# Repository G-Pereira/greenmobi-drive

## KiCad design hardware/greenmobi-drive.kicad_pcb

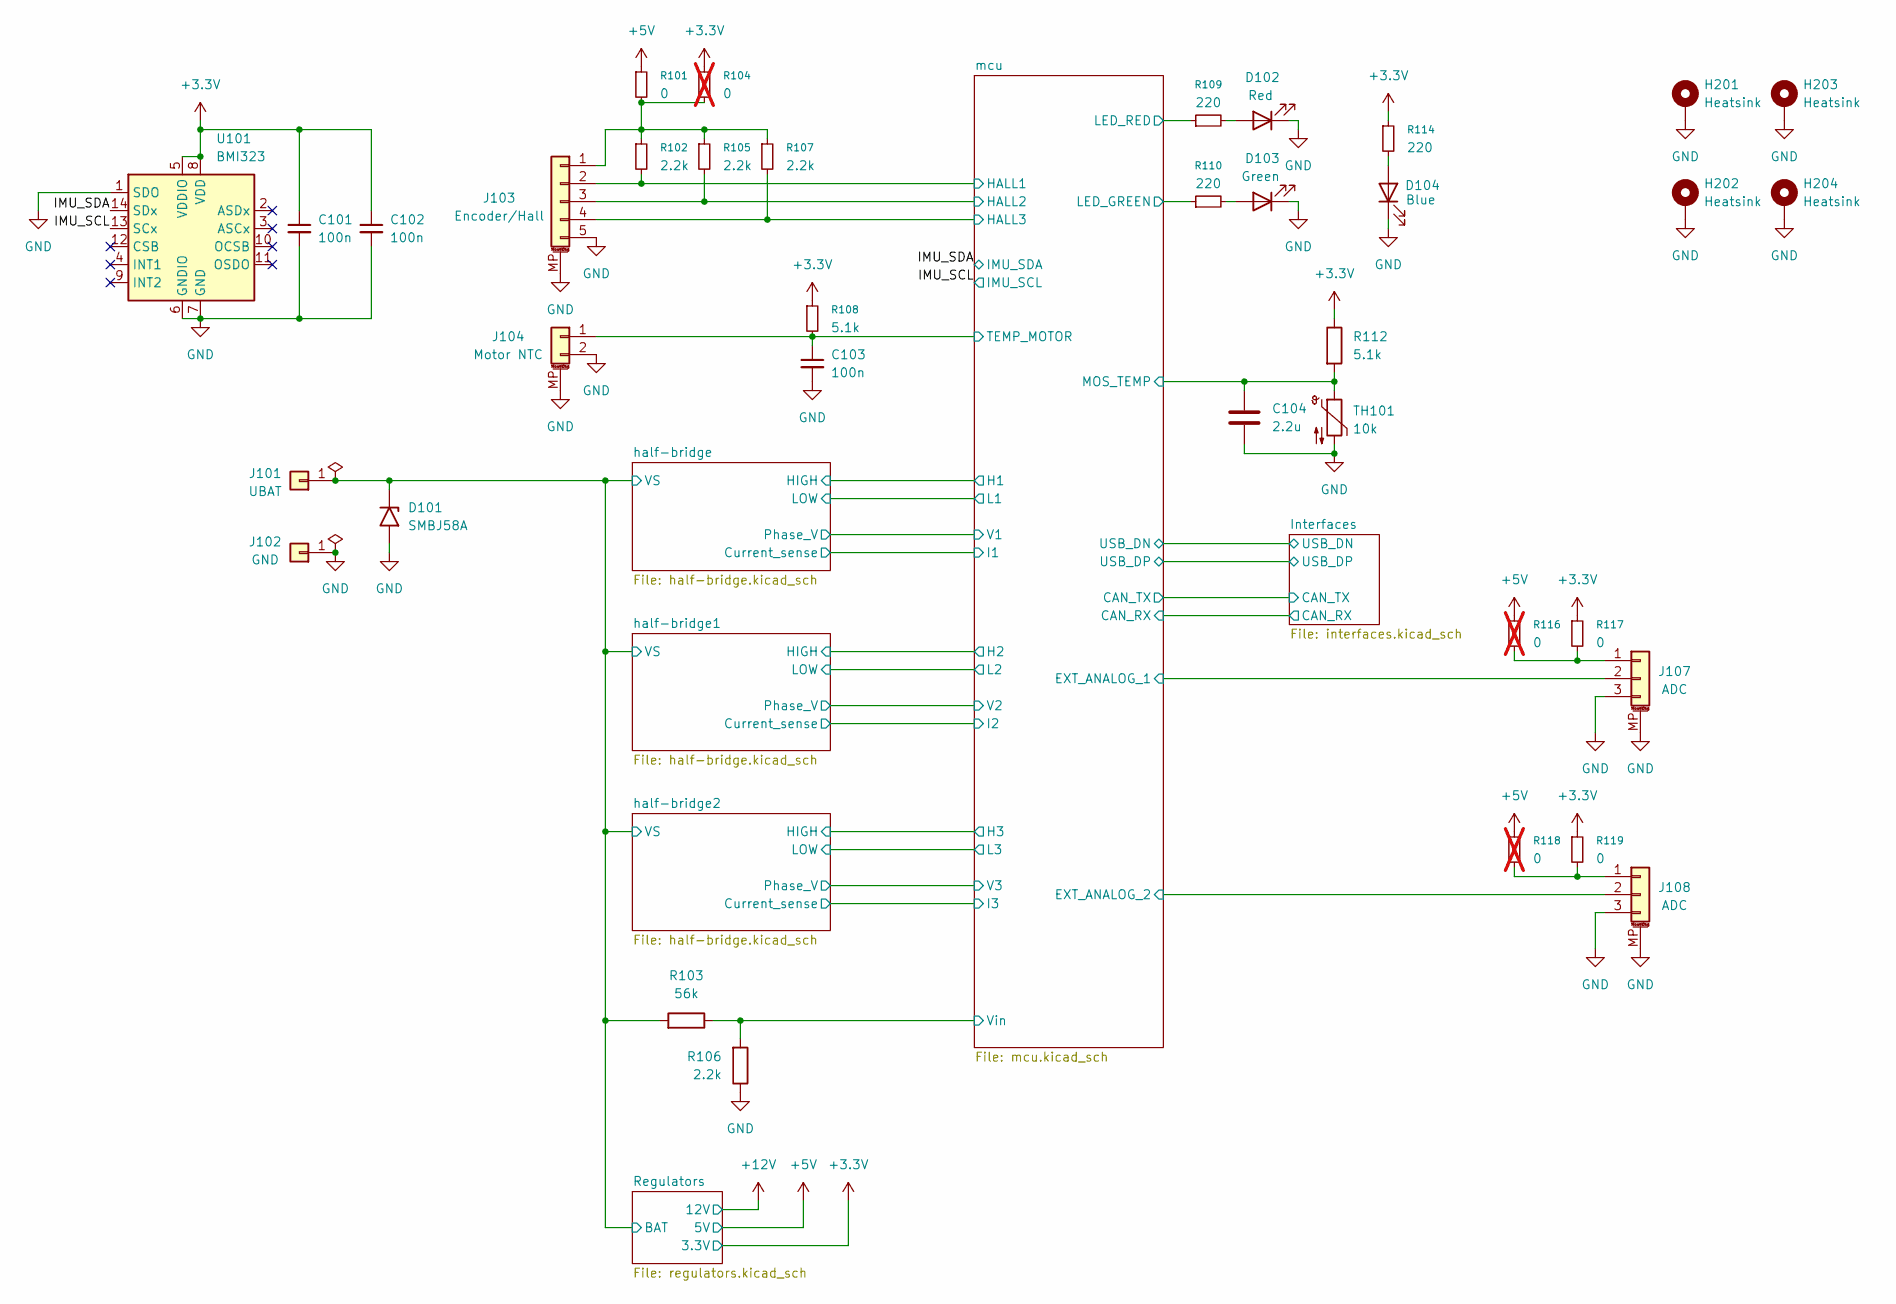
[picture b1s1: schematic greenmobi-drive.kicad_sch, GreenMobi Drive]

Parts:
C101, C102, C103: 100n; C_0402_1005Metric; LCSC C77020
C104: 2.2u; C_0402_1005Metric; LCSC C170151
D101: SMBJ58A; D_SMB; LCSC C151910
D102: Red; LED_0805_2012Metric; LCSC C688884
D103: Green; LED_0805_2012Metric; LCSC C688883
D104: Blue; LED_0805_2012Metric; LCSC C779459
H201, H202, H203, H204: Heatsink; MountingHole_3.2mm_M3_Pad
J101: UBAT; MountingHole_3.2mm_M3_ISO14580_Pad_TopBottom
J102: GND; MountingHole_3.2mm_M3_ISO14580_Pad_TopBottom
J103: Encoder/Hall; JST_PH_B5B-PH-SM4-TB_1x05-1MP_P2.00mm_Vertical; LCSC C17700383
J104: Motor NTC; JST_PH_B2B-PH-SM4-TB_1x02-1MP_P2.00mm_Vertical; LCSC C17700380
J107, J108: ADC; JST_PH_B3B-PH-SM4-TB_1x03-1MP_P2.00mm_Vertical; LCSC C17700383
R101, R117, R119: 0; R_0402_1005Metric; LCSC C106231
R102, R105, R106, R107: 2.2k; R_0402_1005Metric; LCSC C114762
R103: 56k; R_0805_2012Metric; LCSC C17756
R104, R116, R118: 0; R_0402_1005Metric; LCSC C106231; not fitted
R108, R112: 5.1k; R_0402_1005Metric; LCSC C25905
R109, R110, R114: 220; R_0402_1005Metric; LCSC C2909336
TH101: 10k; R_0402_1005Metric; LCSC C77131
U101: BMI323; Bosch_LGA-14_3x2.5mm_P0.5mm; LCSC C5368700

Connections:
+3.3V: C101.1, C102.1, R104.1, R108.1, R112.1, R114.1, R117.1, R119.1, U101.5 (VDDIO), U101.8 (VDD); also elsewhere on the board
+5V: R101.1, R116.1, R118.1; also elsewhere on the board
/IMU_SCL: U101.13 (SCx); also elsewhere on the board
/IMU_SDA: U101.14 (SDx); also elsewhere on the board
/Regulators/BAT: D101.1 (A1), J101.1, R103.2; also elsewhere on the board
/mcu/EXT_ANALOG_1: J107.2; also elsewhere on the board
/mcu/EXT_ANALOG_2: J108.2; also elsewhere on the board
/mcu/HALL1: J103.2, R102.2; also elsewhere on the board
/mcu/HALL2: J103.3, R105.2; also elsewhere on the board
/mcu/HALL3: J103.4, R107.2; also elsewhere on the board
/mcu/LED_GREEN: R110.1; also elsewhere on the board
/mcu/LED_RED: R109.1; also elsewhere on the board
/mcu/MOS_TEMP: C104.1, R112.2, TH101.1; also elsewhere on the board
/mcu/TEMP_MOTOR: C103.1, J104.1, R108.2; also elsewhere on the board
/mcu/Vin: R103.1, R106.2; also elsewhere on the board
GND: C101.2, C102.2, C103.2, C104.2, D101.2 (A2), D102.1 (K), D103.1 (K), D104.1 (K), H201.1, H202.1, H203.1, H204.1, J102.1, J103.5, J103.MP (MountPin), J104.2, J104.MP (MountPin), J107.3, J107.MP (MountPin), J108.3, J108.MP (MountPin), R106.1, TH101.2, U101.1 (SDO), U101.6 (GNDIO), U101.7 (GND); also elsewhere on the board
unnamed: D102.2 (A), R109.2
unnamed: D103.2 (A), R110.2
unnamed: D104.2 (A), R114.2
unnamed: J103.1, R101.2, R102.1, R104.2, R105.1, R107.1
unnamed: J107.1, R116.2, R117.2
unnamed: J108.1, R118.2, R119.2

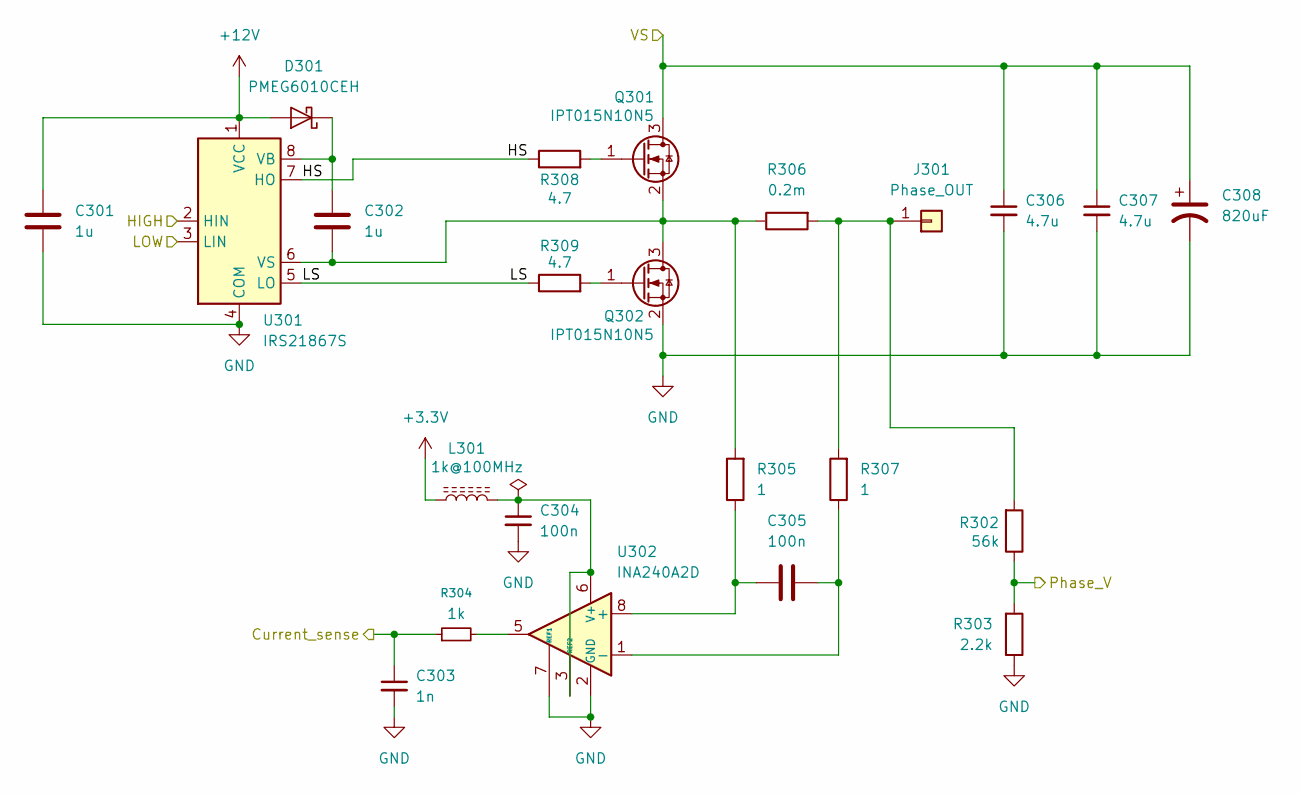
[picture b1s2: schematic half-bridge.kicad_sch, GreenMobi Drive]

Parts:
C301, C302: 1u; C_1206_3216Metric; LCSC C28322
C303: 1n; C_0402_1005Metric
C304, C305: 100n; C_0402_1005Metric; LCSC C77020
C306, C307: 4.7u; C_1210_3225Metric; LCSC C381466
C308: 820uF; CP_Radial_D18.0mm_P7.50mm; LCSC C700880
D301: PMEG6010CEH; D_SOD-123F; LCSC C110797
J301: Phase_OUT; SolderWirePad_1x01_SMD_4x8mm
L301: 1k@100MHz; L_0402_1005Metric; LCSC C76883
Q301, Q302: IPT015N10N5; Infineon_PG-HSOF-8-1_ThermalVias; LCSC C108964
R302: 56k; R_0805_2012Metric; LCSC C17756
R303: 2.2k; R_0402_1005Metric; LCSC C114762
R304: 1k; R_0402_1005Metric
R305, R307: 1; R_0402_1005Metric; LCSC C185446
R306: 0.2m; R_2512_6332Metric; LCSC C4944115
R308, R309: 4.7; R_0603_1608Metric; LCSC C25121
U301: IRS21867S; SOIC-8_3.9x4.9mm_P1.27mm; LCSC C52290
U302: INA240A2D; SOIC-8_3.9x4.9mm_P1.27mm; LCSC C2060768

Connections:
+3.3V: L301.1; also elsewhere on the board
+12V: C301.1, D301.2 (A), U301.1 (VCC); also elsewhere on the board
/Regulators/BAT: C306.1, C307.1, C308.1, Q301.3 (D); also elsewhere on the board
/half-bridge/Current_sense: C303.1, R304.1; also elsewhere on the board
/half-bridge/HIGH: U301.2 (HIN); also elsewhere on the board
/half-bridge/HS: R308.1, U301.7 (HO)
/half-bridge/LOW: U301.3 (LIN); also elsewhere on the board
/half-bridge/LS: R309.1, U301.5 (LO)
/half-bridge/Phase_V: R302.1, R303.2; also elsewhere on the board
GND: C301.2, C303.2, C304.2, C306.2, C307.2, C308.2, Q302.2 (S), R303.1, U301.4 (COM), U302.2 (GND), U302.4 (GND), U302.7 (REF1); also elsewhere on the board
unnamed: C302.1, D301.1 (K), U301.8 (VB)
unnamed: J301.1, R302.2, R306.2, R307.2
unnamed: Q301.1 (G), R308.2
unnamed: C302.2, Q301.2 (S), Q302.3 (D), R305.2, R306.1, U301.6 (VS)
unnamed: Q302.1 (G), R309.2
unnamed: R304.2, U302.5
unnamed: C305.2, R305.1, U302.8 (+)
unnamed: C305.1, R307.1, U302.1 (-)
unnamed: C304.1, L301.2, U302.3 (REF2), U302.6 (V+)

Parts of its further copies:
C401, C402, C501, C502: 1u; C_1206_3216Metric; LCSC C28322
C403, C503: 1n; C_0402_1005Metric
C404, C405, C504, C505: 100n; C_0402_1005Metric; LCSC C77020
C406, C407, C506, C507: 4.7u; C_1210_3225Metric; LCSC C381466
C408, C508: 820uF; CP_Radial_D18.0mm_P7.50mm; LCSC C700880
D401, D501: PMEG6010CEH; D_SOD-123F; LCSC C110797
J401, J501: Phase_OUT; SolderWirePad_1x01_SMD_4x8mm
L401, L501: 1k@100MHz; L_0402_1005Metric; LCSC C76883
Q401, Q402, Q501, Q502: IPT015N10N5; Infineon_PG-HSOF-8-1_ThermalVias; LCSC C108964
R402, R502: 56k; R_0805_2012Metric; LCSC C17756
R403, R503: 2.2k; R_0402_1005Metric; LCSC C114762
R404, R504: 1k; R_0402_1005Metric
R405, R407, R505, R507: 1; R_0402_1005Metric; LCSC C185446
R406, R506: 0.2m; R_2512_6332Metric; LCSC C4944115
R408, R409, R508, R509: 4.7; R_0603_1608Metric; LCSC C25121
U401, U501: IRS21867S; SOIC-8_3.9x4.9mm_P1.27mm; LCSC C52290
U402, U502: INA240A2D; SOIC-8_3.9x4.9mm_P1.27mm; LCSC C2060768

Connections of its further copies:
+3.3V: L401.1, L501.1; also elsewhere on the board
+12V: C401.1, C501.1, D401.2 (A), D501.2 (A), U401.1 (VCC), U501.1 (VCC); also elsewhere on the board
/Regulators/BAT: C406.1, C407.1, C408.1, C506.1, C507.1, C508.1, Q401.3 (D), Q501.3 (D); also elsewhere on the board
/half-bridge1/Current_sense: C403.1, R404.1; also elsewhere on the board
/half-bridge1/HIGH: U401.2 (HIN); also elsewhere on the board
/half-bridge1/HS: R408.1, U401.7 (HO)
/half-bridge1/LOW: U401.3 (LIN); also elsewhere on the board
/half-bridge1/LS: R409.1, U401.5 (LO)
/half-bridge1/Phase_V: R402.1, R403.2; also elsewhere on the board
/half-bridge2/Current_sense: C503.1, R504.1; also elsewhere on the board
/half-bridge2/HIGH: U501.2 (HIN); also elsewhere on the board
/half-bridge2/HS: R508.1, U501.7 (HO)
/half-bridge2/LOW: U501.3 (LIN); also elsewhere on the board
/half-bridge2/LS: R509.1, U501.5 (LO)
/half-bridge2/Phase_V: R502.1, R503.2; also elsewhere on the board
GND: C401.2, C403.2, C404.2, C406.2, C407.2, C408.2, C501.2, C503.2, C504.2, C506.2, C507.2, C508.2, Q402.2 (S), Q502.2 (S), R403.1, R503.1, U401.4 (COM), U402.2 (GND), U402.4 (GND), U402.7 (REF1), U501.4 (COM), U502.2 (GND), U502.4 (GND), U502.7 (REF1); also elsewhere on the board
unnamed: C402.1, D401.1 (K), U401.8 (VB)
unnamed: C502.1, D501.1 (K), U501.8 (VB)
unnamed: J401.1, R402.2, R406.2, R407.2
unnamed: J501.1, R502.2, R506.2, R507.2
unnamed: Q401.1 (G), R408.2
unnamed: C402.2, Q401.2 (S), Q402.3 (D), R405.2, R406.1, U401.6 (VS)
unnamed: Q402.1 (G), R409.2
unnamed: Q501.1 (G), R508.2
unnamed: C502.2, Q501.2 (S), Q502.3 (D), R505.2, R506.1, U501.6 (VS)
unnamed: Q502.1 (G), R509.2
unnamed: R404.2, U402.5
unnamed: R504.2, U502.5
unnamed: C405.2, R405.1, U402.8 (+)
unnamed: C405.1, R407.1, U402.1 (-)
unnamed: C404.1, L401.2, U402.3 (REF2), U402.6 (V+)
unnamed: C505.2, R505.1, U502.8 (+)
unnamed: C505.1, R507.1, U502.1 (-)
unnamed: C504.1, L501.2, U502.3 (REF2), U502.6 (V+)

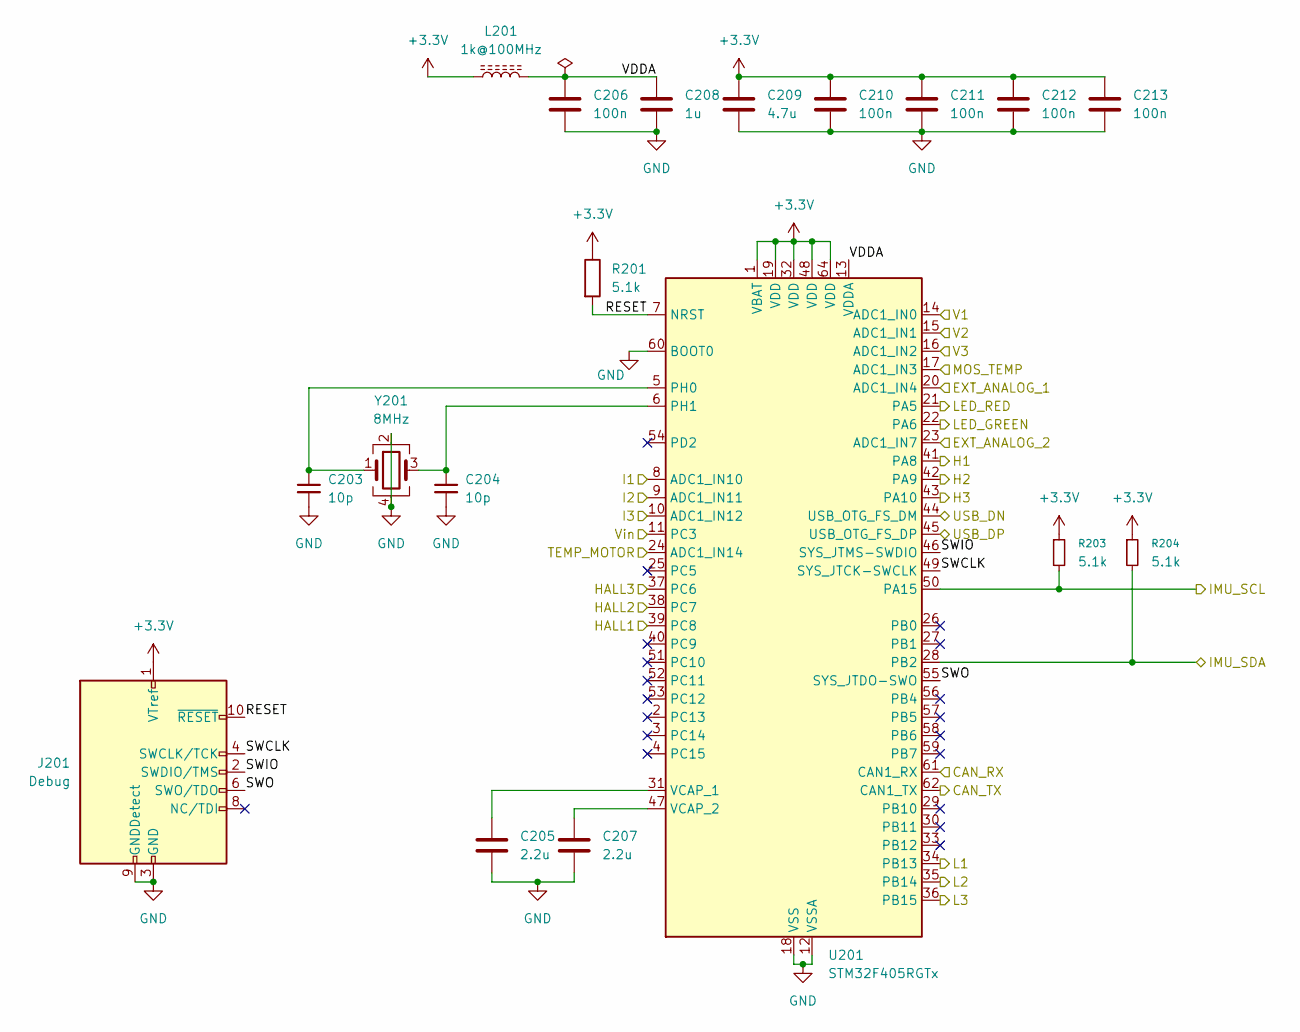
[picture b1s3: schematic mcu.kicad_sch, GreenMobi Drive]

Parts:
C203, C204: 10p; C_0402_1005Metric; LCSC C526994
C205, C207: 2.2u; C_0402_1005Metric; LCSC C170151
C206, C210, C211, C212, C213: 100n; C_0402_1005Metric; LCSC C77020
C208: 1u; C_0402_1005Metric; LCSC C14445
C209: 4.7u; C_0402_1005Metric; LCSC C23733
J201: Debug; PinHeader_2x05_P1.27mm_Vertical_SMD; LCSC C150517
L201: 1k@100MHz; L_0402_1005Metric; LCSC C76883
R201, R203, R204: 5.1k; R_0402_1005Metric; LCSC C25905
U201: STM32F405RGTx; LQFP-64_10x10mm_P0.5mm; LCSC C15742
Y201: 8MHz; Crystal_SMD_3225-4Pin_3.2x2.5mm; LCSC C400090

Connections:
+3.3V: C209.1, C210.1, C211.1, C212.1, C213.1, J201.1 (VTref), L201.1, R201.1, R203.1, R204.1, U201.1 (VBAT), U201.19 (VDD), U201.32 (VDD), U201.48 (VDD), U201.64 (VDD); also elsewhere on the board
/IMU_SCL: R203.2, U201.50 (PA15); also elsewhere on the board
/IMU_SDA: R204.2, U201.28 (PB2); also elsewhere on the board
/Interfaces/CAN_RX: U201.61 (CAN1_RX); also elsewhere on the board
/Interfaces/CAN_TX: U201.62 (CAN1_TX); also elsewhere on the board
/Interfaces/USB_DN: U201.44 (USB_OTG_FS_DM); also elsewhere on the board
/Interfaces/USB_DP: U201.45 (USB_OTG_FS_DP); also elsewhere on the board
/half-bridge1/Current_sense: U201.9 (ADC1_IN11); also elsewhere on the board
/half-bridge1/HIGH: U201.42 (PA9); also elsewhere on the board
/half-bridge1/LOW: U201.35 (PB14); also elsewhere on the board
/half-bridge1/Phase_V: U201.15 (ADC1_IN1); also elsewhere on the board
/half-bridge2/Current_sense: U201.10 (ADC1_IN12); also elsewhere on the board
/half-bridge2/HIGH: U201.43 (PA10); also elsewhere on the board
/half-bridge2/LOW: U201.36 (PB15); also elsewhere on the board
/half-bridge2/Phase_V: U201.16 (ADC1_IN2); also elsewhere on the board
/half-bridge/Current_sense: U201.8 (ADC1_IN10); also elsewhere on the board
/half-bridge/HIGH: U201.41 (PA8); also elsewhere on the board
/half-bridge/LOW: U201.34 (PB13); also elsewhere on the board
/half-bridge/Phase_V: U201.14 (ADC1_IN0); also elsewhere on the board
/mcu/EXT_ANALOG_1: U201.20 (ADC1_IN4); also elsewhere on the board
/mcu/EXT_ANALOG_2: U201.23 (ADC1_IN7); also elsewhere on the board
/mcu/HALL1: U201.39 (PC8); also elsewhere on the board
/mcu/HALL2: U201.38 (PC7); also elsewhere on the board
/mcu/HALL3: U201.37 (PC6); also elsewhere on the board
/mcu/LED_GREEN: U201.22 (PA6); also elsewhere on the board
/mcu/LED_RED: U201.21 (PA5); also elsewhere on the board
/mcu/MOS_TEMP: U201.17 (ADC1_IN3); also elsewhere on the board
/mcu/RESET: J201.10 (~RESET), R201.2, U201.7 (NRST)
/mcu/SWCLK: J201.4 (SWCLK/TCK), U201.49 (SYS_JTCK-SWCLK)
/mcu/SWIO: J201.2 (SWDIO/TMS), U201.46 (SYS_JTMS-SWDIO)
/mcu/SWO: J201.6 (SWO/TDO), U201.55 (SYS_JTDO-SWO)
/mcu/TEMP_MOTOR: U201.24 (ADC1_IN14); also elsewhere on the board
/mcu/VDDA: C206.1, C208.1, L201.2, U201.13 (VDDA)
/mcu/Vin: U201.11 (PC3); also elsewhere on the board
GND: C203.2, C204.2, C205.2, C206.2, C207.2, C208.2, C209.2, C210.2, C211.2, C212.2, C213.2, J201.3 (GND), J201.5 (GND), J201.9 (GNDDetect), U201.12 (VSSA), U201.18 (VSS), U201.60 (BOOT0), U201.63 (VSS), Y201.2, Y201.4; also elsewhere on the board
unnamed: C203.1, U201.5 (PH0), Y201.1
unnamed: C204.1, U201.6 (PH1), Y201.3
unnamed: C205.1, U201.31 (VCAP_1)
unnamed: C207.1, U201.47 (VCAP_2)

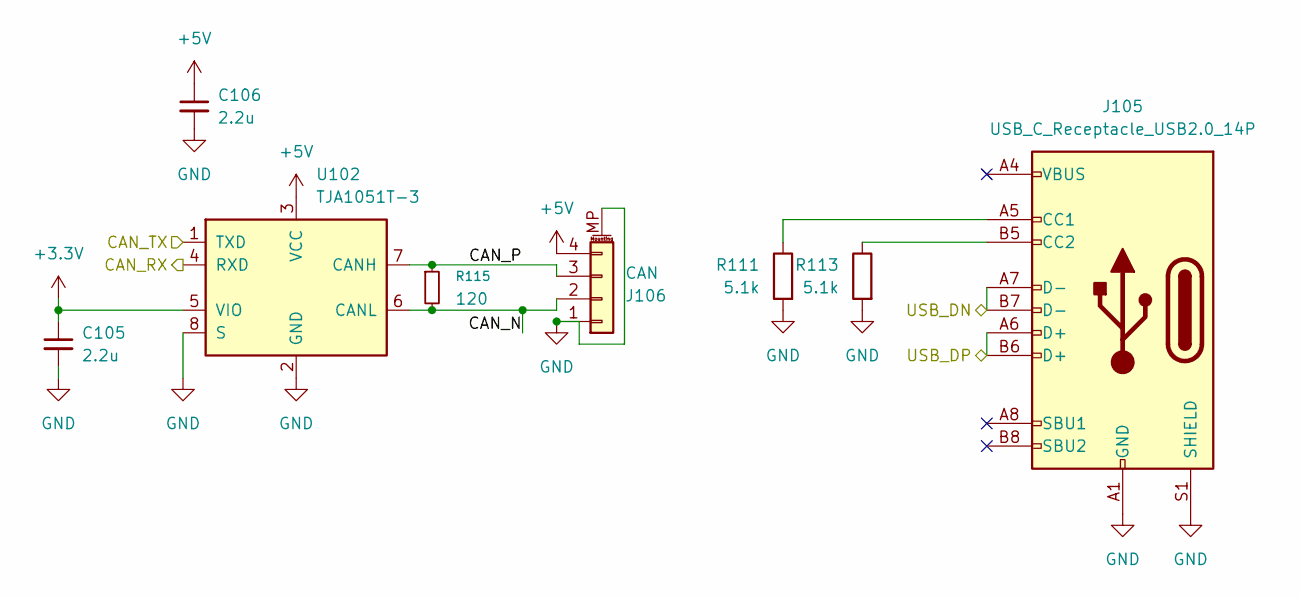
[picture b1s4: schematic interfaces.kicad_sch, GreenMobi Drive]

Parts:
C105, C106: 2.2u; C_0402_1005Metric; LCSC C170151
J105: USB_C_Receptacle_USB2.0_14P; USB_C_Receptacle_Palconn_UTC16-G; LCSC C2765186
J106: CAN; JST_PH_B4B-PH-SM4-TB_1x04-1MP_P2.00mm_Vertical; LCSC C17700382
R111, R113: 5.1k; R_0402_1005Metric; LCSC C25905
R115: 120; R_0402_1005Metric; LCSC C25079
U102: TJA1051T-3; SOIC-8_3.9x4.9mm_P1.27mm; LCSC C38695

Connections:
+3.3V: C105.1, U102.5 (VIO); also elsewhere on the board
+5V: C106.1, J106.4, U102.3 (VCC); also elsewhere on the board
/Interfaces/CAN_N: J106.2, R115.2, U102.6 (CANL)
/Interfaces/CAN_P: J106.3, R115.1, U102.7 (CANH)
/Interfaces/CAN_RX: U102.4 (RXD); also elsewhere on the board
/Interfaces/CAN_TX: U102.1 (TXD); also elsewhere on the board
/Interfaces/USB_DN: J105.A7 (D-), J105.B7 (D-); also elsewhere on the board
/Interfaces/USB_DP: J105.A6 (D+), J105.B6 (D+); also elsewhere on the board
GND: C105.2, C106.2, J105.A1 (GND), J105.A12 (GND), J105.B1 (GND), J105.B12 (GND), J105.S1 (SHIELD), J106.1, J106.MP (MountPin), R111.2, R113.2, U102.2 (GND), U102.8 (S); also elsewhere on the board
unnamed: J105.A5 (CC1), R111.1
unnamed: J105.B5 (CC2), R113.1

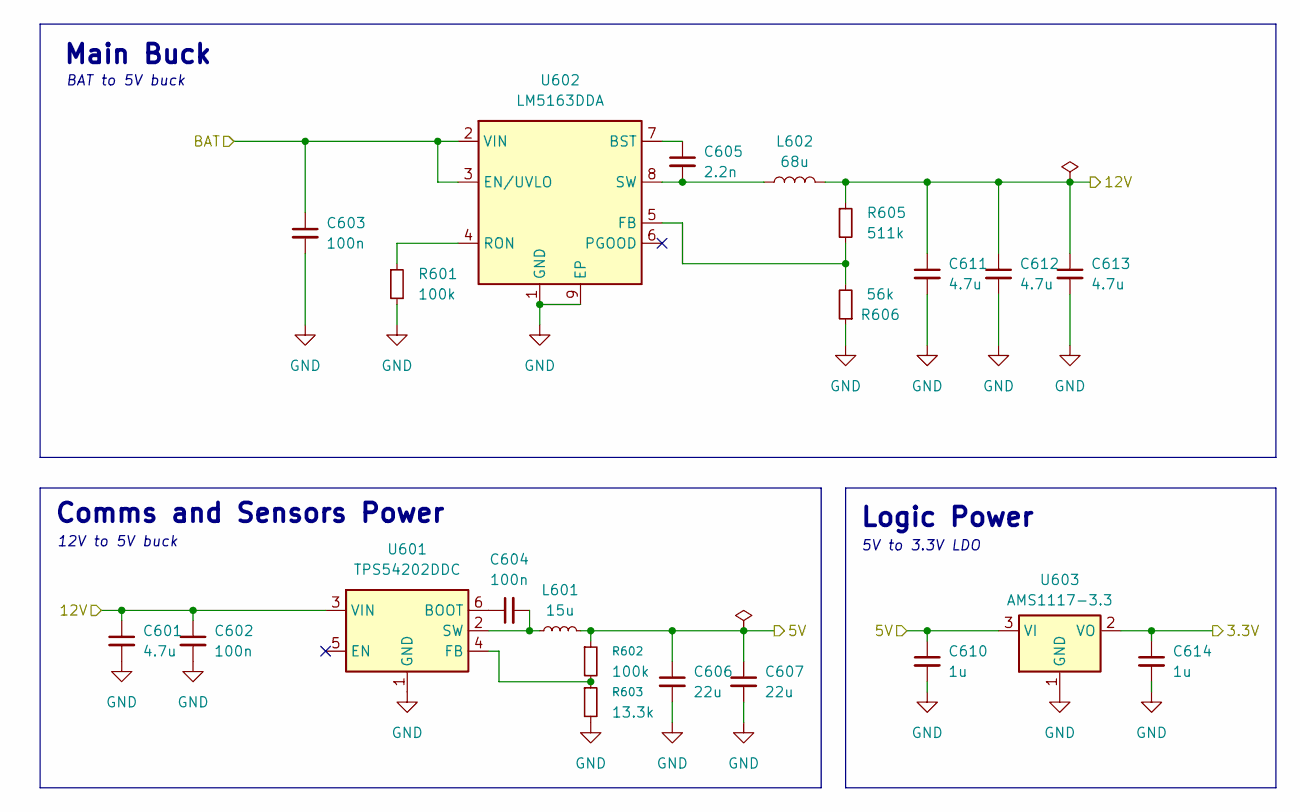
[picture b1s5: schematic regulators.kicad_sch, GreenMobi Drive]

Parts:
C601, C611, C612, C613: 4.7u; C_0805_2012Metric; LCSC C1779
C602, C604: 100n; C_0402_1005Metric; LCSC C77020
C603: 100n; C_1206_3216Metric; LCSC C110255
C605: 2.2n; C_0402_1005Metric; LCSC C106861
C606, C607: 22u; C_0805_2012Metric; LCSC C45783
C610, C614: 1u; C_1206_3216Metric; LCSC C28322
L601: 15u; L_Chilisin_BMRA00040420; LCSC C2894719
L602: 68u; L_KOHERelec_MDA7030; LCSC C2894721
R601, R602: 100k; R_0402_1005Metric; LCSC C60491
R603: 13.3k; R_0402_1005Metric; LCSC C2974007
R605: 511k; R_0603_1608Metric; LCSC C2930114
R606: 56k; R_0805_2012Metric; LCSC C17756
U601: TPS54202DDC; SOT-23-6; LCSC C191884
U602: LM5163DDA; HSOP-8-1EP_3.9x4.9mm_P1.27mm_EP2.41x3.1mm_ThermalVias; LCSC C2873264
U603: AMS1117-3.3; SOT-223-3_TabPin2; LCSC C6186

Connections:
+3.3V: C614.1, U603.2 (VO); also elsewhere on the board
+5V: C606.1, C607.1, C610.1, L601.2, R602.1, U603.3 (VI); also elsewhere on the board
+12V: C601.1, C602.1, C611.1, C612.1, C613.1, L602.2, R605.1, U601.3 (VIN); also elsewhere on the board
/Regulators/BAT: C603.1, U602.2 (VIN), U602.3 (EN/UVLO); also elsewhere on the board
GND: C601.2, C602.2, C603.2, C606.2, C607.2, C610.2, C611.2, C612.2, C613.2, C614.2, R601.2, R603.2, R606.1, U601.1 (GND), U602.1 (GND), U602.9 (EP), U603.1 (GND); also elsewhere on the board
unnamed: C604.1, U601.6 (BOOT)
unnamed: R602.2, R603.1, U601.4 (FB)
unnamed: C604.2, L601.1, U601.2 (SW)
unnamed: C605.1, U602.7 (BST)
unnamed: R605.2, R606.2, U602.5 (FB)
unnamed: R601.1, U602.4 (RON)
unnamed: C605.2, L602.1, U602.8 (SW)

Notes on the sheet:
Logic Power
5V to 3.3V LDO
BAT to 5V buck
Comms and Sensors Power
Main Buck
12V to 5V buck

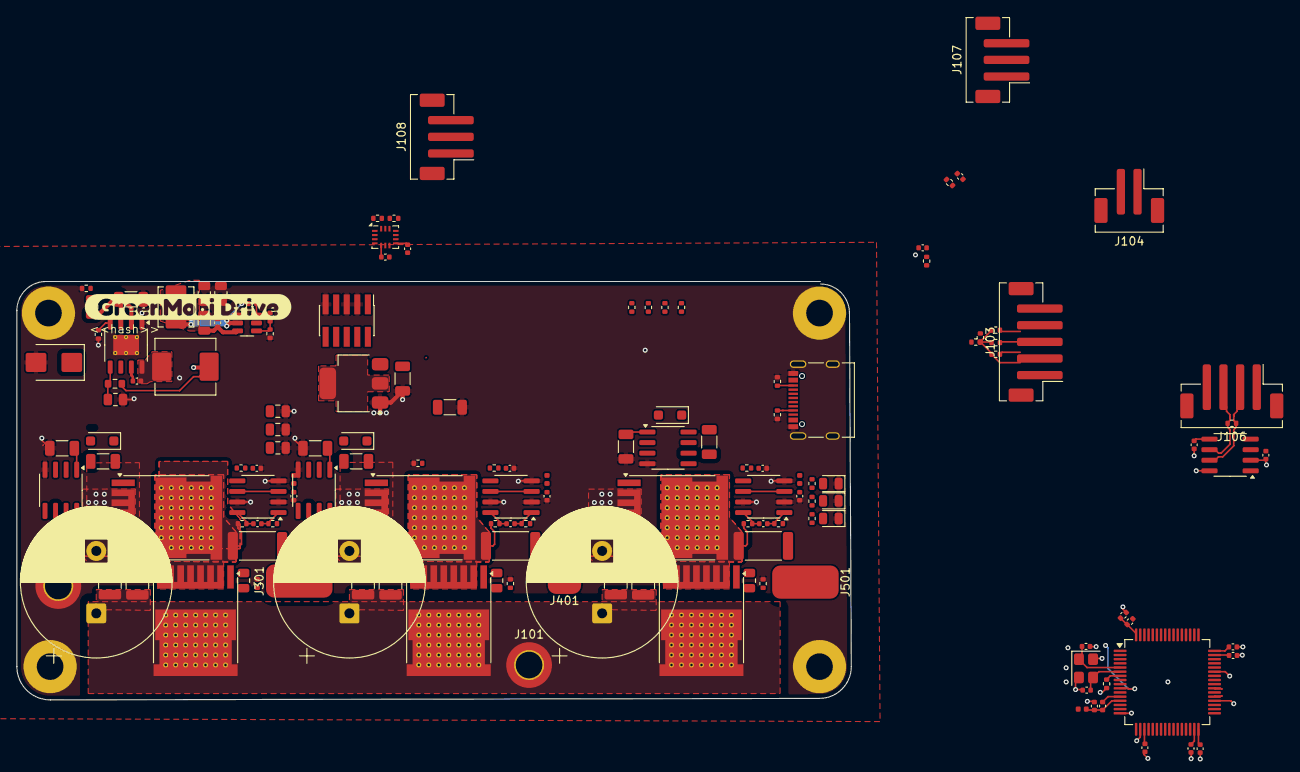
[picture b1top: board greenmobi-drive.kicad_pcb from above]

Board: 2 copper layers, 100.3 x 50.3 mm, 154 parts (0 on the bottom side), 92 nets.

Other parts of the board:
kibuzzard-68C90E22: G***; kibuzzard-68C90E22

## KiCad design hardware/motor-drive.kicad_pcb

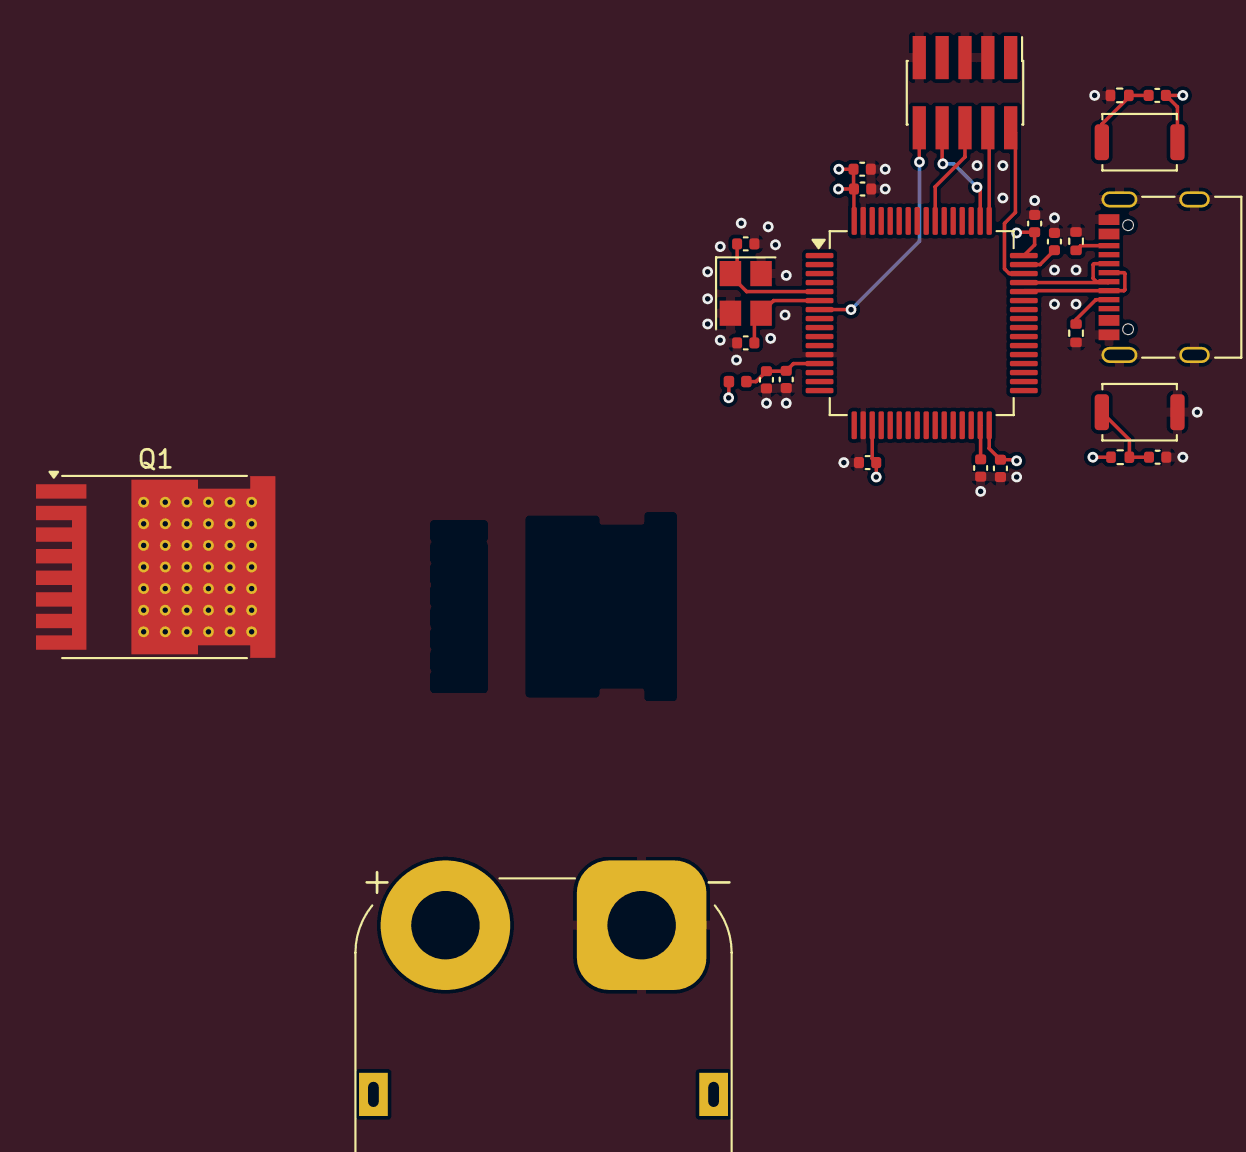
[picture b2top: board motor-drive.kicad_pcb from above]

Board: 4 copper layers, 26 parts (0 on the bottom side), 17 nets.

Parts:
C1, C3, C4, C5, C6, C10, C13: 100n; C_0402_1005Metric
C2: 1u; C_0402_1005Metric
C7: 4.7u; C_0402_1005Metric
C8, C9: 2.2u; C_0402_1005Metric
C11, C12: 10p; C_0402_1005Metric
J1: USB_C_Receptacle_USB2.0_14P; USB_C_Receptacle_Palconn_UTC16-G
J2: Debug; PinHeader_2x05_P1.27mm_Vertical_SMD
J3: BAT; AMASS_XT90PW-M_1x02_P10.90mm_Horizontal
L1: L_Ferrite; L_0402_1005Metric
Q1: NMOS; Infineon_PG-HSOF-8-1_ThermalVias
R1, R2, R3, R4: 5.1k; R_0402_1005Metric
SW1: RESET; SW_Push_SPST_NO_Alps_SKRK
SW2: BOOT; SW_Push_SPST_NO_Alps_SKRK
U1: STM32F405RGTx; LQFP-64_10x10mm_P0.5mm
Y1: 8MHz; Crystal_SMD_3225-4Pin_3.2x2.5mm

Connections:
+3.3V: C3.1, C4.1, C5.1, C6.1, C7.1, C13.1, J2.1 (VTref), L1.1, R1.1, SW2.2, U1.1 (VBAT), U1.19 (VDD), U1.32 (VDD), U1.48 (VDD), U1.64 (VDD)
/USB_DN: J1.A7 (D-), J1.B7 (D-), U1.44 (USB_OTG_FS_DM)
/USB_DP: J1.A6 (D+), J1.B6 (D+), U1.45 (USB_OTG_FS_DP)
/mcu/BOOT: C13.2, R2.1, SW2.1, U1.60 (BOOT0)
/mcu/RESET: C10.1, J2.10 (~RESET), R1.2, SW1.2, U1.7 (NRST)
/mcu/SWCLK: J2.4 (SWCLK/TCK), U1.49 (SYS_JTCK-SWCLK)
/mcu/SWIO: J2.2 (SWDIO/TMS), U1.46 (SYS_JTMS-SWDIO)
/mcu/SWO: J2.6 (SWO/TDO), U1.55 (SYS_JTDO-SWO)
/mcu/TDI: J2.8 (NC/TDI), U1.50 (SYS_JTDI)
/mcu/VDDA: C1.1, C2.1, L1.2, U1.13 (VDDA)
GND: C1.2, C2.2, C3.2, C4.2, C5.2, C6.2, C7.2, C8.2, C9.2, C10.2, C11.2, C12.2, J1.A1 (GND), J1.A12 (GND), J1.B1 (GND), J1.B12 (GND), J1.S1 (SHIELD), J2.3 (GND), J2.5 (GND), J2.9 (GNDDetect), J3.1, R2.2, R3.2, R4.2, SW1.1, U1.12 (VSSA), U1.18 (VSS), U1.63 (VSS), Y1.2, Y1.4
unnamed: J1.A5 (CC1), R4.1
unnamed: J1.B5 (CC2), R3.1
unnamed: C12.1, U1.5 (PH0), Y1.1
unnamed: C11.1, U1.6 (PH1), Y1.3
unnamed: C9.1, U1.31 (VCAP_1)
unnamed: C8.1, U1.47 (VCAP_2)

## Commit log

2025-03-09 MCU schematic
2025-03-09 Define footprints
2025-03-09 MCU layout
2025-03-09 Added power connector
2025-03-09 Started work on half bridges
2025-06-04 Add CAN, USB and sensors
2025-06-04 Add a board edge to test CI
2025-06-04 Install zip on CI
2025-06-04 Simplified CI
2025-06-04 Remove sudo from CI
2025-06-04 Update LICENSE
2025-06-04 FIx CI
2025-06-08 half bridges
2025-06-08 phase capacitors
2025-07-01 Placement study
2025-07-05 Power Layout
2025-07-05 Layout
2025-07-08 Added IMU
2025-07-08 5V regulator
2025-07-22 Regulators layout
2025-07-24 Placement complete
2025-07-30 Layout mostly done
2025-07-31 BOM optimizations
2025-08-02 Mounting holes alignment
2025-08-02 Remove soldermask under heat critical components
2025-08-02 Avoid zip inside zip
2025-08-02 Round corners
2025-08-02 Move traces away from USB
2025-08-02 Capacitors sourced
2025-08-02 Fix Release Artifacts
2025-08-02 Sourcing complete
2025-08-02 Fix Release export
2025-08-28 Add software configs
2025-08-28 Fix LCSC part number on regulator output caps
2025-08-28 Add missing I2C pullups
2025-08-31 Change power connections to pads instead of holes
2025-08-31 Allow CI to attach files to releases
2025-08-31 Remove file export from repo
2025-08-31 Remove log file
2025-08-31 Make DRC happy
2025-08-31 Make CI check DRC
2025-08-31 Disable DRC check for now and activate ERC
2025-08-31 Revert "Allow CI to attach files to releases"
    This reverts commit b270502710a3843402cecd3094dd57504ff374fd.
2025-08-31 Test report kibot output
2025-09-03 Reduce gate MOSFET current
2025-09-08 TVS and eletrolythic cap
2025-09-08 Change solder wire pads
2025-09-09 Added external analog inputs
2025-09-09 Removed buttons for boot and reset
2025-09-11 CI disable verbose logs
2025-09-11 ERC exclusions
2025-09-15 Changed bootstrap resistor to 0 Ohm
2025-09-15 Reduce board size
2025-09-15 Test fit on 50x100mm
2025-09-22 Changed bootstrap diode and gate resistor
2025-09-25 Layout work
2025-09-25 HW limits set on software to use bench PSU
